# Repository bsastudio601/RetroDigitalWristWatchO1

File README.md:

# RetroDigitalWristWatchO1
A Retro Futuristic wrist watch inspired from nixie tube wrist watch.

# CAD 

The link to onshape file :

```bash
https://cad.onshape.com/documents/2ff11cee5ddfbc3f83090756/w/65dea8c705ea60074a3121a2/e/956382457094d7dfe0466492?renderMode=0&uiState=6ae2dc71c6980aea61bdc922
```

## total assembly

This is the look im aiming for !

## case

this is the middle section or the main body of the watch 

This is the bottom plate. the bottom plate has magnetic connector for charging

This is the top plate and its suppose to hold a 1 mm thick 40mm watch crystal.

# PCB 

THE PCB ! (took a few tries to get a decent routing for 2 layer pcb)

And the schematic 

# Assembly
The case is really precise and there in very little room for fancy connection system to put the case together im thinking to superrglue the top and glass to the body. there is going to be a grove to aling them. and same goes for the bottom but without the glue.

# Firmware
Currently the firmware includes a really basic code to test the displays i need to get the components to update the code to work it properly with all the functions

# BOM

| # | Component | Quantity |
|---:|---|---:|
| 1 | Seeed Studio XIAO ESP32-C3 | 1 |
| 2 | 0.2-inch single-digit SMD 7-segment display, common-cathode | 4 |
| 3 | 74HC595 shift register | 2 |
| 4 | LIS3DH 3-axis accelerometer | 1 |
| 5 | 1S LiPo battery | 1 |
| 6 | 4.7 kΩ resistor | 2 |
| 7 | 100 nF ceramic capacitor | 3 |
| 8 | 10 µF ceramic capacitor | 1 |
| 9 | magnetic connector 2 pin | 1 set |
| 10 | Custom 2-layer PCB | 1 |
| 11 | Watch case | 1 |
| 12 | Watch crystal/lens | 1 |
| 13 | 20 mm watch strap | 1 |
| 14 | Spring bars | 2 |

# Conclusion 
It was one of the hardest project for me because i had to learn Onshape and CAD from groundup. and the pcb routing took a few tries to make it work in 2 layer. But it was done with the help of gpt on helping me to choose right symbol in kicad and helping me navigate cad software.

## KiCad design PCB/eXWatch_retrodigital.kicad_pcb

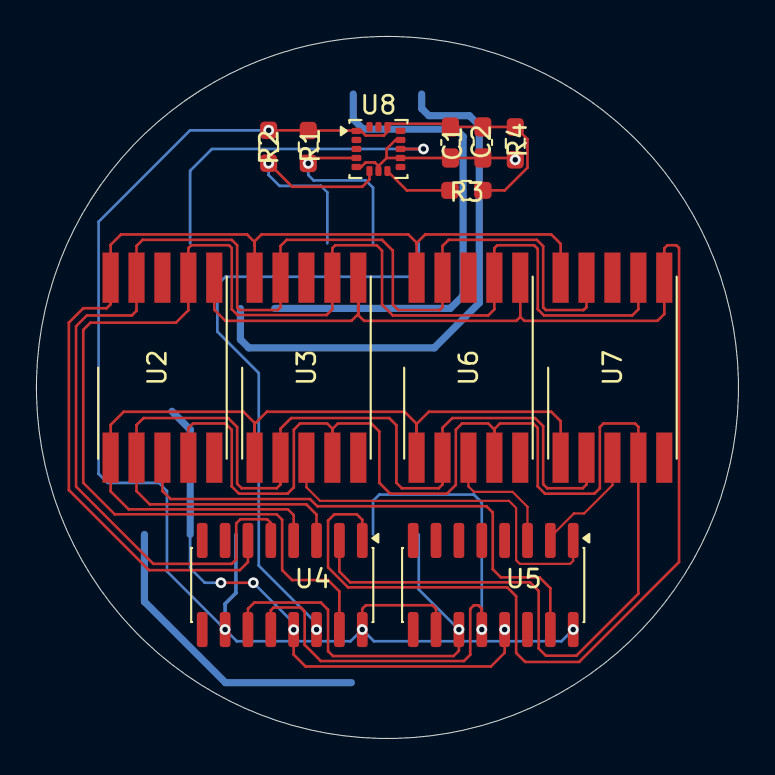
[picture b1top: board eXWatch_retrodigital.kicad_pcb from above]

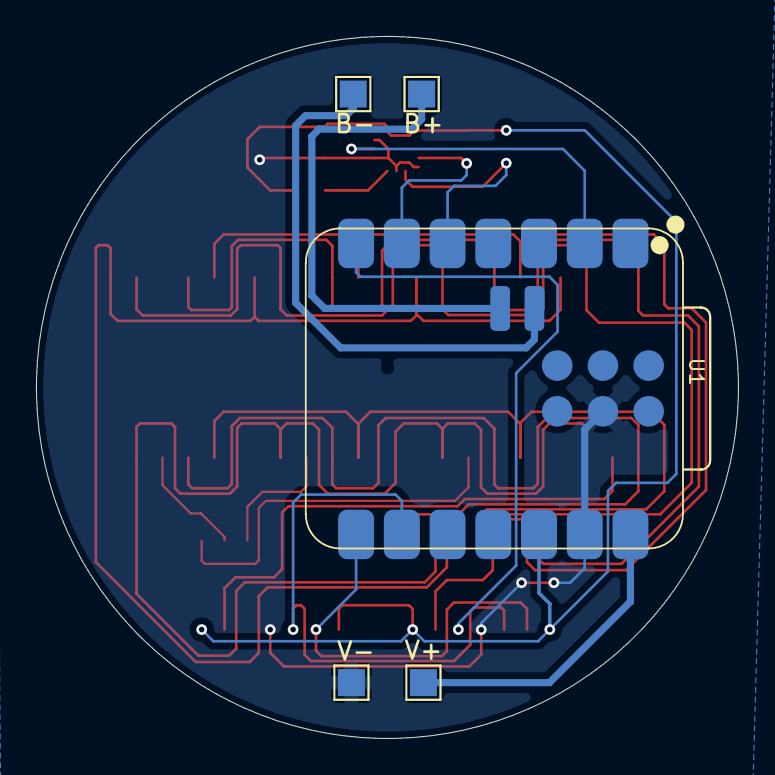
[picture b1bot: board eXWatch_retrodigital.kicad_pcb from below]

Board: 4 copper layers, 39.0 x 39.0 mm, 18 parts (5 on the bottom side), 24 nets.

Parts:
B+: TestPoint; TestPoint_Pad_1.5x1.5mm
B-: TestPoint; TestPoint_Pad_1.5x1.5mm
C1: 0.1uF; C_0603_1608Metric_Pad1.08x0.95mm_HandSolder
C2: 10uF; C_0603_1608Metric_Pad1.08x0.95mm_HandSolder
R1, R2: 4.7K; R_0603_1608Metric_Pad0.98x0.95mm_HandSolder
R3, R4: 10K; R_0603_1608Metric_Pad0.98x0.95mm_HandSolder
U1: XIAO-ESP32-C3-SMD
U2, U3, U6, U7: KCSC02-105
U4, U5: 74HC595; SOIC-16_3.9x9.9mm_P1.27mm
U8: LIS3DH; LGA-16_3x3mm_P0.5mm_LayoutBorder3x5y
V+: TestPoint; TestPoint_Pad_1.5x1.5mm
V-: TestPoint; TestPoint_Pad_1.5x1.5mm

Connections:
+3.3V: C1.1, C2.1, R1.1, R2.1, R3.1, R4.1, U1.12 (3V3_OUT), U4.10 (~SRCLR), U4.16 (VCC), U5.10 (~SRCLR), U5.16 (VCC), U8.1 (VDD_IO), U8.14 (VDD)
/A: U2.7 (A), U3.7 (A), U4.15 (QA), U6.7 (A), U7.7 (A)
/B: U2.6 (B), U3.6 (B), U4.1 (QB), U6.6 (B), U7.6 (B)
/C: U2.4 (C), U3.4 (C), U4.2 (QC), U6.4 (C), U7.4 (C)
/CC1: U2.3 (CC), U5.15 (QA)
/CC2: U3.3 (CC), U5.1 (QB)
/CC3: U5.2 (QC), U7.3 (CC)
/CC4: U5.3 (QD), U6.3 (CC)
/D: U2.2 (D), U3.2 (D), U4.3 (QD), U6.2 (D), U7.2 (D)
/D6: U1.7 (D6), U4.14 (SER)
/D7: U1.8 (D7), U4.11 (SRCLK), U5.11 (SRCLK)
/D8: U1.9 (D8), U4.12 (RCLK), U5.12 (RCLK)
/E: U2.1 (E), U3.1 (E), U4.4 (QE), U6.1 (E), U7.1 (E)
/F: U2.9 (F), U3.9 (F), U4.5 (QF), U6.9 (F), U7.9 (F)
/G: U2.10 (G), U3.10 (G), U4.6 (QG), U6.10 (G), U7.10 (G)
/INT1: U1.2 (D1), U8.11 (INT1)
/SCL/A: R1.2, U1.6 (D5), U8.4 (SPC)
/SDA/A: R2.2, U1.5 (D4), U8.6 (SDI)
GND: C1.2, C2.2, R4.2, U1.13 (GND), U1.18 (GND), U4.8 (GND), U4.13 (~OE), U5.8 (GND), U5.13 (~OE), U8.5 (GND), U8.7 (SDO), U8.10 (GND), U8.12 (GND), V-.1 (1_1)
unnamed: B-.1 (1_1), U1.22 (GND)
unnamed: B+.1 (1_1), U1.21 (VBAT)
unnamed: U1.14 (VBUS), V+.1 (1_1)
unnamed: U4.9 (QH'), U5.14 (SER)
unnamed: R3.2, U8.8 (CS)
